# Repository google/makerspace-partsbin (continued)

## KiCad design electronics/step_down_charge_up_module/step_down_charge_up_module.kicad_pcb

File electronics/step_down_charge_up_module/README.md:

# Step-down-charge-up module

## Status

Estimated current: about 3A
Status: boards fabbed, untested

## Known issues

I2C port is at vbat, which needs a level translator.

## Background

This board's goal is to be a Pi UPS, while also allowing configurable powerup
behavior and battery voltage monitoring (that can be used as a crude estimate
of capacity).  Existing Pi UPS options were inadequate because they either:

* Don't have configurable behavior on power returning
* Don't monitor battery charge at all
* Don't have a failsafe timer after setting the GPIO that should
  software-shutdown
* Weren't open-source enough

By including an attiny, we should see extremely low quiescent current, and
allows for restarting (e.g. periodically, once an hour) or other more complex
behavior in software.

Eventually I hope to shrink this down to a module that can be pre-built and
included on other boards.

## Similar reading

The TP5410 IC does most of what this does, but at lower currents.  Look into
that if you are simply powering a MCU.

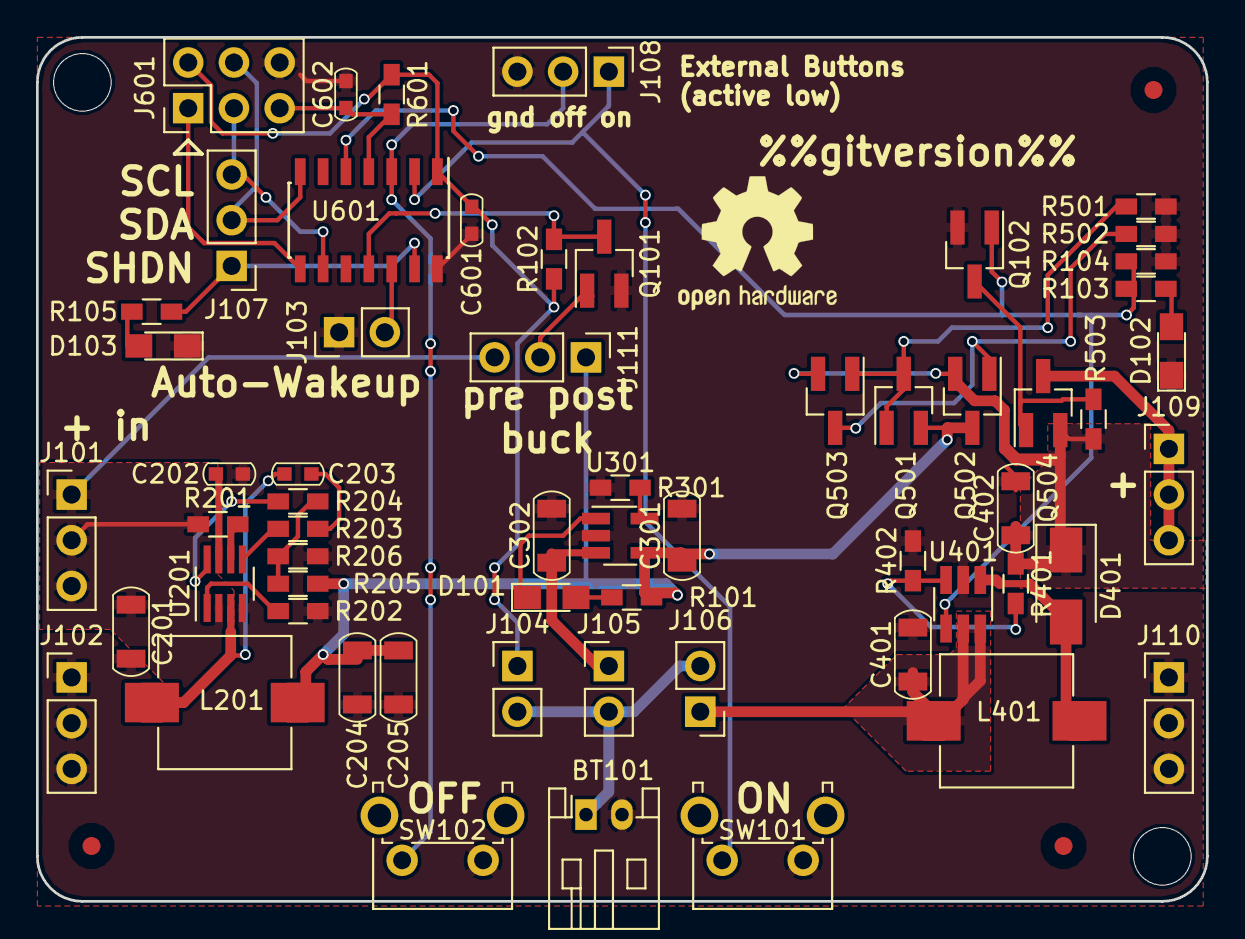
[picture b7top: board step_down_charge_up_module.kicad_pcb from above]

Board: 2 copper layers, 65.0 x 48.0 mm, 65 parts (0 on the bottom side), 38 nets.

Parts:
BT101: Battery_Cell; JST_PH_S2B-PH-K_02x2.00mm_Angled
C201, C204, C205, C401: 22u; C_1206
C202, C203, C601, C602: 0.1u; C_0603
C301, C302: 4.7u; C_1206
C402: 10u; C_1206
D101, D102, D103: LED; LED_0805_HandSoldering
D401: D_Schottky; D_SMA
J101, J102, J107, J108, J109, J110, J111: CONN_01X03; Pin_Header_Straight_1x03_Pitch2.54mm
J103, J104, J105, J106: CONN_01X02; Pin_Header_Straight_1x02_Pitch2.54mm
J601: CONN_02X03; Pin_Header_Straight_2x03_Pitch2.54mm
L201: 4.7u; L_7.3x7.3_Handsoldering
L401: L; L_7.3x7.3_Handsoldering
P101: Outline; Board_Outline_65x48mm
P102: OSHW; OSHW-Logo2_9.8x8mm_SilkScreen
P103, P104, P105: Fid; Fiducial_1mm_Dia_2.54mm_Outer_CopperTop
Q101, Q102: Q_NMOS_GSD; SOT-23_Handsoldering
Q501, Q503: 2N3906; SOT-23_Handsoldering
Q502: AO3401A; SOT-23_Handsoldering
Q504: Q_PMOS_GSD; SOT-23_Handsoldering
R101, R103, R105: 1k; R_0603_HandSoldering
R102, R104: 1M; R_0603_HandSoldering
R201, R503, R601: 100k; R_0603_HandSoldering
R202: 75k; R_0603_HandSoldering
R203: 20R; R_0603_HandSoldering
R204: 20k; R_0603_HandSoldering
R205: 40.2k; R_0603_HandSoldering
R206: 7.5k; R_0603_HandSoldering
R301: 2k; R_0603_HandSoldering
R401: 267k; R_0603_HandSoldering
R402: 34.8k; R_0603_HandSoldering
R501: 10k; R_0603_HandSoldering
R502: 47k; R_0603_HandSoldering
SW101, SW102: SW_Push; SW_Tactile_SPST_Angled_PTS645Vx58-2LFS
U201: MP2315; SOT-23-8_Handsoldering
U301: MCP73831; SOT-23-5_HandSoldering
U401: SX1308; SOT-23-6_Handsoldering
U601: ATTINY84-20SSU; SOIC-14_3.9x8.7mm_Pitch1.27mm

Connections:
/charge/BATT: C302.1, J105.1, U301.3
/charge/CHG_PWR: C204.1, C205.1, C301.1, J111.1, L201.2, Q501.2, Q502.3, R101.1, R205.2, U301.4
/charge/~CHARGING: D101.1, U301.1
/load_switch/BOOSTED_BATT_IN: C402.1, D401.1, Q502.2, Q503.2, Q504.2, R401.1, R503.1
/load_switch/OUT: J109.1, J109.2, J109.3, Q504.3
/load_switch/~EN: Q102.3, Q504.1, R503.2
/step_down/PWR_IN: C201.1, J101.1, J101.2, J101.3, J111.3, R201.1, U201.2
/step_up/PWR_IN: C401.1, J106.1, L401.1, U401.5, U401.6
/supervisor/5V_EN: Q102.1, R103.1, R104.1, U401.4, U601.5
/supervisor/BATT: C601.1, J104.1, J601.2, R102.1, R601.1, U601.1
/supervisor/MISO: J601.1, U601.8
/supervisor/RESET: C602.1, J601.5, R601.2, U601.4
/supervisor/SCL: J107.3, J601.3, U601.9
/supervisor/SDA: J107.2, J601.4, U601.7
/supervisor/SHUTDOWN: J107.1, R105.1, U601.13
/supervisor/~OFF_BUTTON: J108.2, SW102.2, U601.3
/supervisor/~ON_BUTTON: J108.1, SW101.2, U601.2
/supervisor/~ON_WALL: Q101.3, R102.2, U601.11
/supervisor/~WAKEUP_ON_RETURN: J103.2, U601.12
GND: BT101.2, C201.2, C202.2, C204.2, C205.2, C301.2, C302.2, C401.2, C402.2, C601.2, C602.2, D102.1, D103.1, J102.1, J102.2, J102.3, J103.1, J108.3, J110.1, J110.2, J110.3, J601.6, Q101.2, Q102.2, R104.2, R202.2, R206.1, R301.1, R402.2, R501.2, R502.2, SW101.1, SW102.1, U201.4, U301.2, U401.2, U601.14
unnamed: BT101.1, J104.2, J105.2, J106.2
unnamed: C202.1, U201.7
unnamed: C203.1, R203.1
unnamed: C203.2, L201.1, U201.3
unnamed: D101.2, R101.2
unnamed: D102.2, R103.2
unnamed: D103.2, R105.2
unnamed: D401.2, L401.2, U401.1
unnamed: J111.2, Q101.1
unnamed: Q501.1, Q501.3, Q503.1, R501.1
unnamed: Q502.1, Q503.3, R502.1
unnamed: R201.2, U201.6
unnamed: R202.1, U201.1
unnamed: R203.2, U201.5
unnamed: R204.1, R205.1, R206.2
unnamed: R204.2, U201.8
unnamed: R301.2, U301.5
unnamed: R401.2, R402.1, U401.3

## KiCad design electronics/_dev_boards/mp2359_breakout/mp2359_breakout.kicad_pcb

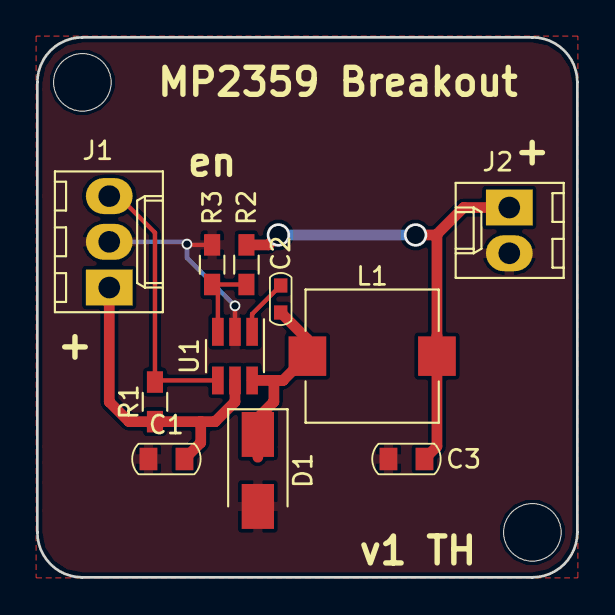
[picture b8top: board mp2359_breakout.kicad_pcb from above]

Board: 2 copper layers, 30.0 x 30.0 mm, 12 parts (0 on the bottom side), 7 nets.

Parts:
C1: 10u; C_0805
C2: C; C_0603
C3: 22u; C_0805
D1: D_Schottky; D_SMA
J1: CONN_01X03; Molex_KK-6410-03_03x2.54mm_Straight
J2: CONN_01X02; Molex_KK-6410-02_02x2.54mm_Straight
L1: L; L_7.3x7.3_Handsoldering
P1: SYMBOL; Outline_30
R1: 100k; R_0603_HandSoldering
R2: 49.9k; R_0603_HandSoldering
R3: 16.2k; R_0603_HandSoldering
U1: MP2359; SOT-23-6_Handsoldering

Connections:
/Vin: C1.1, J1.1, R1.1, U1.5
/Vout: C3.1, J2.1, L1.2, R2.1
/Vsw: C2.2, D1.1, L1.1, U1.6
GND: C1.2, C3.2, D1.2, J1.2, J2.2, R3.2, U1.2
unnamed: C2.1, U1.1
unnamed: J1.3, R1.2, U1.4
unnamed: R2.2, R3.1, U1.3

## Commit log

2017-04-12 Initial comment to partsbin
2017-04-13 Add gitignore
2017-06-23 Migrate custom kicad libraries to partsbin
2017-06-23 Correct location of EN pin on buckmodule
2017-06-23 Add TP5410
2017-06-23 Add untested TO-220/247 package.
2017-07-08 Add micro relay
2017-07-08 Add tabs
2017-07-08 Add TLV431 shunt regulator
2017-07-08 Add screw connector
2017-07-08 Add small tact switch
2017-07-13 Rename polarity symbols library, fix test
2017-07-13 Add common battery holder
2017-07-13 Slightly better naming for the first buck module
2017-07-13 Add scripts to generate gerbers
2017-07-13 Added breakout board for ER-TFT024-3 TFT screen
2017-07-13 Clean up paths for tft breakout
2017-07-13 Finishg routing tft breakout, including outline
2017-07-13 Swap to HandSoldering versions on tft breakout
2017-07-14 Add some untested devboards I've been kicking around
2017-07-14 Update more libraries
2017-07-25 Add a small ESP8266-based button.
    Depending on solder jumpers, can either wake up from full power down
    using the button, or wake from deep sleep (button does nothing in
    that case).
2017-07-26 Add esp/bmp custom libs
2017-07-26 Add esp button readme
2017-07-26 Begin next button version
2017-07-26 Remove bad copy-paste reference
2017-08-11 Enlarge capacitor pads for easier soldering
2017-08-11 esp_button almost to v1.1
    Easier to solder
    * Mostly 0805, with some 1206 for larger caps
    * Battery connector is your choice of through hole or SMT
    * Fiducials, just in case
    Easier to program
    * Full FTDI connector
2017-08-12 Aesthetic tweaks to esp_button 1.1
2017-08-12 esp_button: fix 3v3 pour, update render
2017-08-15 update pdf
2017-08-16 adding initial checkin of the firmware
2017-08-16 Adding license and README
2017-08-17 Initial smd_class board
2017-08-17 Add MPxxxx generic board for ESOP-8
2017-08-17 smd_class: add ground pour, full url silk
2017-08-17 Finish up MP23xx board
2017-08-17 Move around topmost resistor a bit
2017-09-06 mosfet tester progress
2017-09-06 Checkpoint mosfet tester
2017-09-06 Rework entire board, still in progress
2017-09-06 Add initial mosfet tester
2017-09-06 Ignore autosaves too
2017-09-06 Simple step load
2017-09-07 Cleanup and better Makefile
2017-09-07 mp2359_breakout: properly connect ground
2017-09-07 Beginning of mp2315 buck module
2017-09-07 sync
2017-09-07 checkpoint 2
2017-09-07 Sync with partial layout
2017-09-07 Checkpoint
2017-09-07 Correctly generate symlink; remove extensions within gerbers
2017-09-07 scrub paths
2017-09-07 Minor changes
2017-09-07 Add README for step-down-charge-up
2017-09-07 Finish routing, add ICSP port.
2017-09-07 A couple more footprints I didn't end up using
2017-09-07 Swap LED resistor locations, enlarge handsoldering inductor
2017-09-07 Swap to 1206 caps for easier prototyping.
2017-09-07 Rename mosfet_tester to better march purpose
2017-09-07 Move simple_step_load to subdir
2017-11-13 Update misc libraries, add beginning of a linter
2017-11-14 Add warning symbol to CH340 TX/RX lines.
    I think the datasheet is using a naming scheme that is backwards
    compared to what I'm used to.
2017-11-14 Swap the SMD/TH ordering on PH combo
2017-11-14 Add SOIC-8 and ESP32 module that use vias for exposed pad.
2017-11-15 Add a more obvious test point
2017-12-30 Add some new footprints
2018-01-18 Add two little proto boards
2018-01-18 Turns out -cache.lib is important for versions
    (4.0.6 -> 4.0.7 for example)
2018-01-18 Add hangbot board, in-progress
2018-01-18 Include 0.4mm traces
2018-01-18 Re-layout board to be NEMA-17 sized.
2018-01-24 Swap to trapezoidal pad in TO-220/247 part
2018-02-06 Add custom board outlines for small waterproof boxes.
    Tested by 1:1 printout to be pretty close. Only one of the mounting
    hole spacings isn't a nice round number.
2018-02-07 Rename relay footprint/symbol
2018-02-09 Add stack light board
2018-02-14 Add stitcher script
2018-02-16 Add another waterproof box board
2018-02-23 Add USB housing
2018-02-23 Minor changes, but wire in outliner script
2018-02-27 Add Pi Zero outline
2018-02-27 Add experimental NetTie+Cap part
2018-02-27 Add MP2315
2018-02-28 Move Pi Zero outline to correct layer
2018-03-06 Add square board intended for tic-tac-toe display
2018-03-06 Fix pin mapping on WS2812B
2018-03-07 Make footprint resizer able to resize text
2018-03-07 Add OSHW certification to square_grid_board
2018-03-07 Minor updates on recent boards
2018-04-30 Snapshot yellow bin holder
2018-05-07 Changes to fit Stanley organizers and work more efficiently.
    * Adds back corners for strength
    * Expand width so Stanley organizers can go in
    * Move all rails down so the top slot is usable
    * Enlarge top cutout for fingers through handle
2018-05-07 Add corner piece script
2018-05-11 Add demo pieces for joinery, experimental "hook" support
2018-05-11 Add squareness calibration piece
2018-05-16 Add experimental dust shoe
2018-05-16 Various changes to yellow_bin_rack and joinery
    - Reduce polygon count on small circles.
    - Tweak fingers for back piece so screws don't collide.
    - Joinery test changes
    - Friction-fit changes for slotting fingers
2018-05-28 Updating platformio.ini for new ESP-IDF
    Fix the compile for the new ESP-IDF: https://github.com/esp8266/Arduino/issues/4740
2019-05-29 Updating to python3 Adding IOT Button board Updating to KiCAD 5
2022-06-07 adding repo exemption for allstar security scanner
